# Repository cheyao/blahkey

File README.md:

# Blahkey

Cute blahaj shaped keychain. Who doesn't want one in their hands?

## Schematic

## PCB

Check out https://solder.hackclub.com/ to build a PCB, and get it made for free!

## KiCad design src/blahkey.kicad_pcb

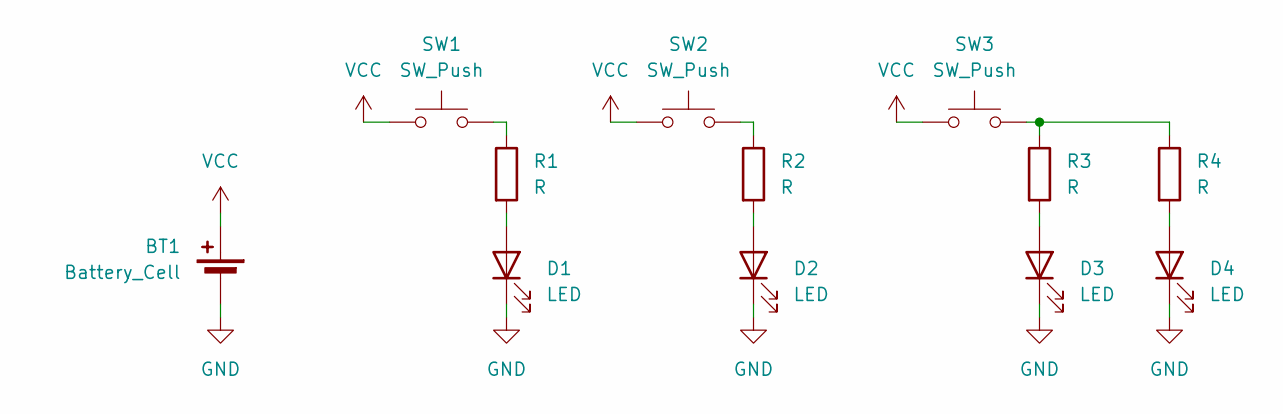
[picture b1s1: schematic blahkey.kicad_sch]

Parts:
BT1: Battery_Cell; BatteryHolder_Multicomp_BC-2001_1x2032
D1, D2, D3, D4: LED; LED_D3.0mm
R1, R2, R3, R4: R; R_Axial_DIN0207_L6.3mm_D2.5mm_P7.62mm_Horizontal
SW1, SW2, SW3: SW_Push; SW_PUSH_6mm

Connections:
GND: BT1.2 (-), D1.1 (K), D2.1 (K), D3.1 (K), D4.1 (K)
unnamed: D1.2 (A), R1.2
unnamed: D2.2 (A), R2.2
unnamed: D3.2 (A), R3.2
unnamed: D4.2 (A), R4.2
unnamed: R1.1, SW1.2
unnamed: R2.1, SW2.2
unnamed: R3.1, R4.1, SW3.2
VCC: BT1.1 (+), SW1.1, SW2.1, SW3.1

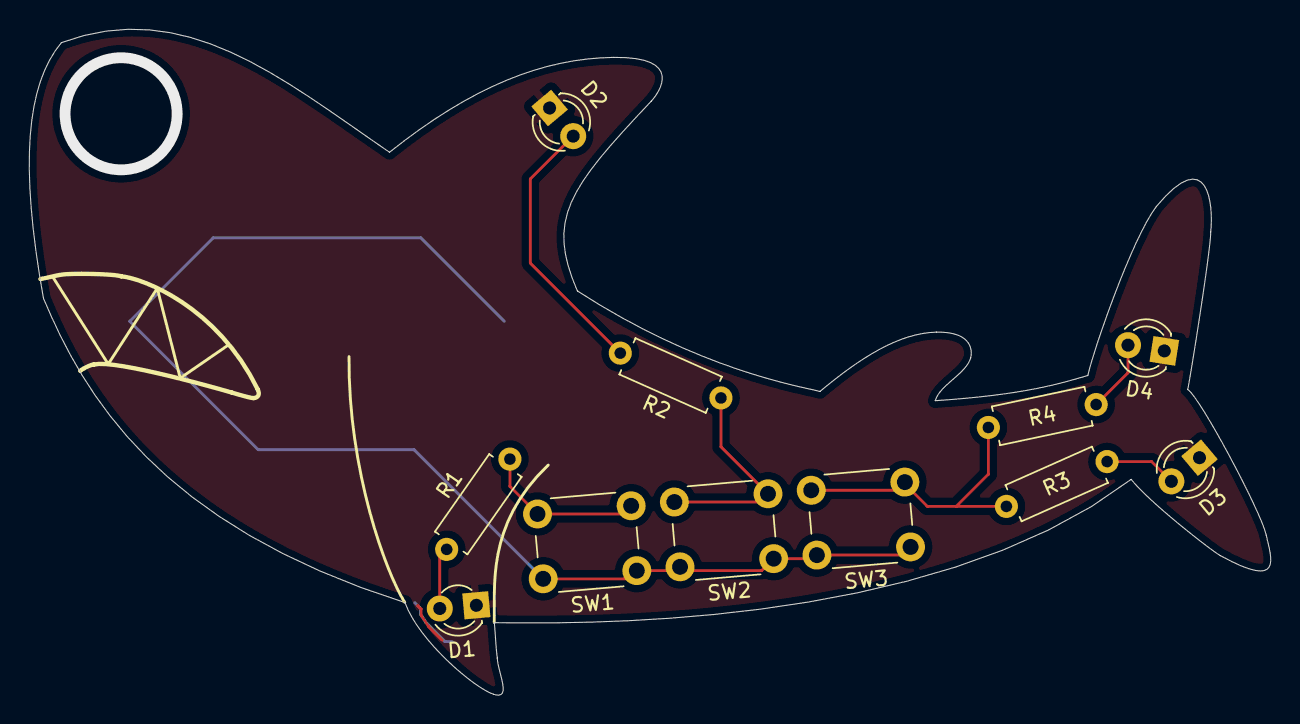
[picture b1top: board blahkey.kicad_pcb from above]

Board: 2 copper layers, 85.8 x 46.0 mm, 12 parts (1 on the bottom side), 9 nets.

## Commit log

2025-04-03 Init
